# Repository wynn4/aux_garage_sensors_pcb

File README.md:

# *GarageGateGuard*
## About
This project contains KiCad 8.0 files and all supporting information needed for you to build your own *GarageGateGuard* PCB to protect the liftgate of your vehicle from having the garage door accidentally closed on it. The *GarageGateGuard* PCB enables you to add an auxiliary pair of infrared sensors to your garage door opening. When the auxiliary sensors are blocked (e.g., by your car's liftgate), power to the infrared transmitter of your opener's primary sensor pair is interrupted--emulating a blockage condition and stopping your opener from closing the door. Regular safety operation of your primary sensors is still maintained.

The PCB is built around a circuit presented by [@0033mer](https://youtube.com/@0033mer?si=xY0d-Dty4cxYaAsI) in a his "Garage Door Safety Sensors" [video](https://youtu.be/CdpjvQUqqL8?si=sJUc2Y0D_GqsPqLC) where he shows how to decode the output of the infrared receiver to determine if the beam from the transmitter is being received or not. In this PCB design, the decoded signal is used to control an NMOS switch which is wired up to control the ON-state of the garage opener's primary infrared transmitter. Full details can be seen in the included schematic and wiring diagram.

## Operation
For the auxiliary sensors, the PCB is designed to use a pair of 6V "universal" garage door safety sensors and has been validated using [these sensors](https://a.co/d/aTHSjK9) from Amazon. In theory the name-brand sensors from LiftMaster, Chamberlain, etc., should also work, but none of these have been tested. Because the system's "interface" with the existing garage door opener is so simple (i.e., just interrupting the ground connection to the opener's existing infrared transmitter), it should work with virtually any opener that has safety sensors powered by DC voltage under 40V (this is the Drain-Source voltage limit of the NMOS). The PCB reqires 6VDC supplied via J1 (see BOM for recommended power supply) and the PWR LED will illuminate to indicate the board is powered-on. When the auxiliary sensors (TXB and RXB) are not within line-of-sight of each other, the BLK (i.e., "blocked") LED will also illuminate. For the PCB to function as designed, a pin-jumper (see BOM) must be placed in the ACT (i.e., "active") position on JP1. If the PCB were to fail, or begin to malfunction, original operation of your garage door could be quickly restored by simply moving the jumper to the BYP (i.e., "bypass") position.

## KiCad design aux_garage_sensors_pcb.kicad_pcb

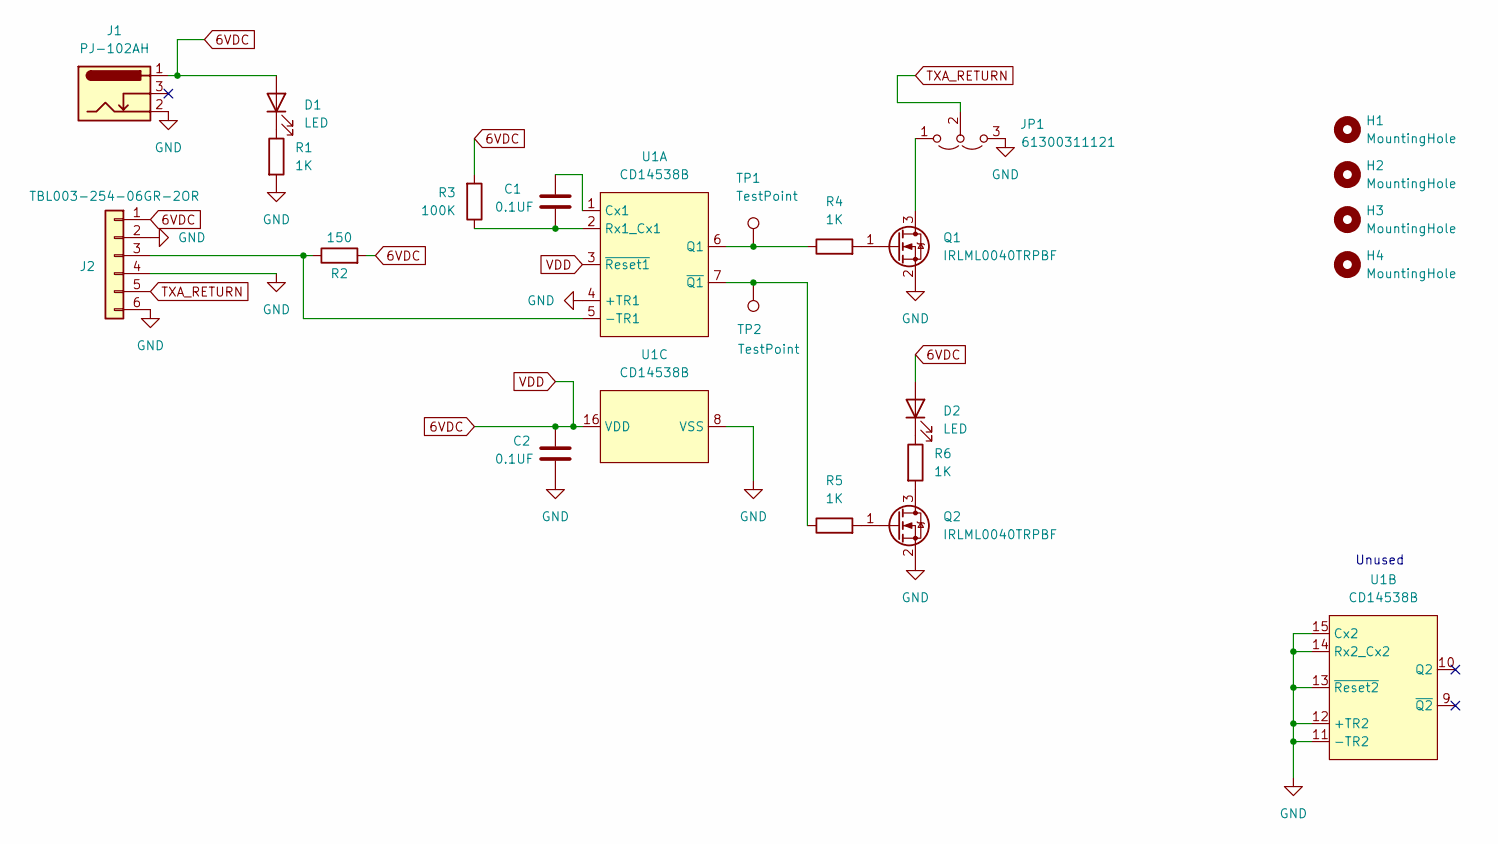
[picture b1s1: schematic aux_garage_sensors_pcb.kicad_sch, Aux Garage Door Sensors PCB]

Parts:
C1, C2: 0.1UF; C_0805_2012Metric_Pad1.18x1.45mm_HandSolder; MPN CL21B104KBCNNNC
D1, D2: LED; LED_0805_2012Metric_Pad1.15x1.40mm_HandSolder; MPN 150080AS75000
H1, H2, H3, H4: MountingHole; MountingHole_3.2mm_M3
J1: PJ-102AH; BarrelJack_Horizontal; MPN PJ-102AH
J2: TBL003-254-06GR-2OR; screwless_terminal_block_01x06; MPN TBL003-254-06GR-2OR
JP1: 61300311121; PinHeader_1x03_P2.54mm_Vertical; MPN 61300311121
Q1, Q2: IRLML0040TRPBF; SOT-23; MPN IRLML0040TRPBF
R1, R4, R5, R6: 1K; R_0805_2012Metric_Pad1.20x1.40mm_HandSolder; MPN RNCP0805FTD1K00
R2: 150; R_0805_2012Metric_Pad1.20x1.40mm_HandSolder; MPN ERJ-P06J151V
R3: 100K; R_0805_2012Metric_Pad1.20x1.40mm_HandSolder; MPN RC0805FR-07100KL
TP1, TP2: TestPoint; TestPoint_Pad_D1.5mm
U1: CD14538B; SOIC-16_3.9x9.9mm_P1.27mm; MPN CD14538BM96

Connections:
6VDC: C2.1, D1.2 (A), D2.2 (A), J1.1, J2.1, R2.2, R3.2, U1.3 (~Reset1), U1.16 (VDD)
GND: C2.2, J1.2, J2.2, J2.4, J2.6, JP1.3 (B), Q1.2 (S), Q2.2 (S), R1.2, U1.4 (+TR1), U1.8 (VSS), U1.11 (-TR2), U1.12 (+TR2), U1.13 (~Reset2), U1.14 (Rx2_Cx2), U1.15 (Cx2)
unnamed: D1.1 (K), R1.1
unnamed: D2.1 (K), R6.1
unnamed: J2.3, R2.1, U1.5 (-TR1)
unnamed: JP1.1 (A), Q1.3 (D)
unnamed: Q1.1 (G), R4.2
unnamed: Q2.3 (D), R6.2
unnamed: Q2.1 (G), R5.2
unnamed: C1.1, U1.1 (Cx1)
unnamed 10: R4.1, TP1.1, U1.6 (Q1); also elsewhere on the board
unnamed: C1.2, R3.1, U1.2 (Rx1_Cx1)
unnamed 12: R5.1, TP2.1, U1.7 (~Q1); also elsewhere on the board
TXA_RETURN: J2.5, JP1.2 (C)

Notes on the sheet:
Unused

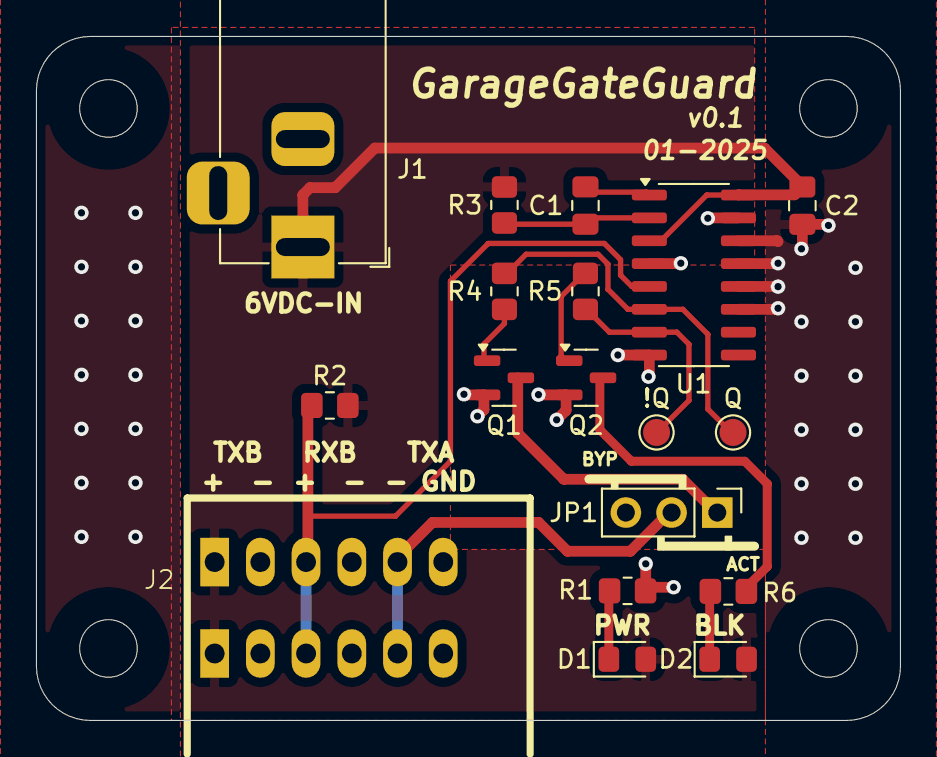
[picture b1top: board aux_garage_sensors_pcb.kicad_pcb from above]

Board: 2 copper layers, 48.0 x 38.0 mm, 22 parts (0 on the bottom side), 14 nets.

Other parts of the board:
!Q: TestPoint; TestPoint_Pad_D1.5mm
Q: TestPoint; TestPoint_Pad_D1.5mm

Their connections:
unnamed 10: Q.1; also elsewhere on the board
unnamed 12: !Q.1; also elsewhere on the board

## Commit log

2025-01-27 adding initial project files
2025-01-27 added date and git info to silkscreen
2025-01-28 added BOM and v0.1 manufacturing files
2025-03-16 added README
2025-03-16 Fix typo
